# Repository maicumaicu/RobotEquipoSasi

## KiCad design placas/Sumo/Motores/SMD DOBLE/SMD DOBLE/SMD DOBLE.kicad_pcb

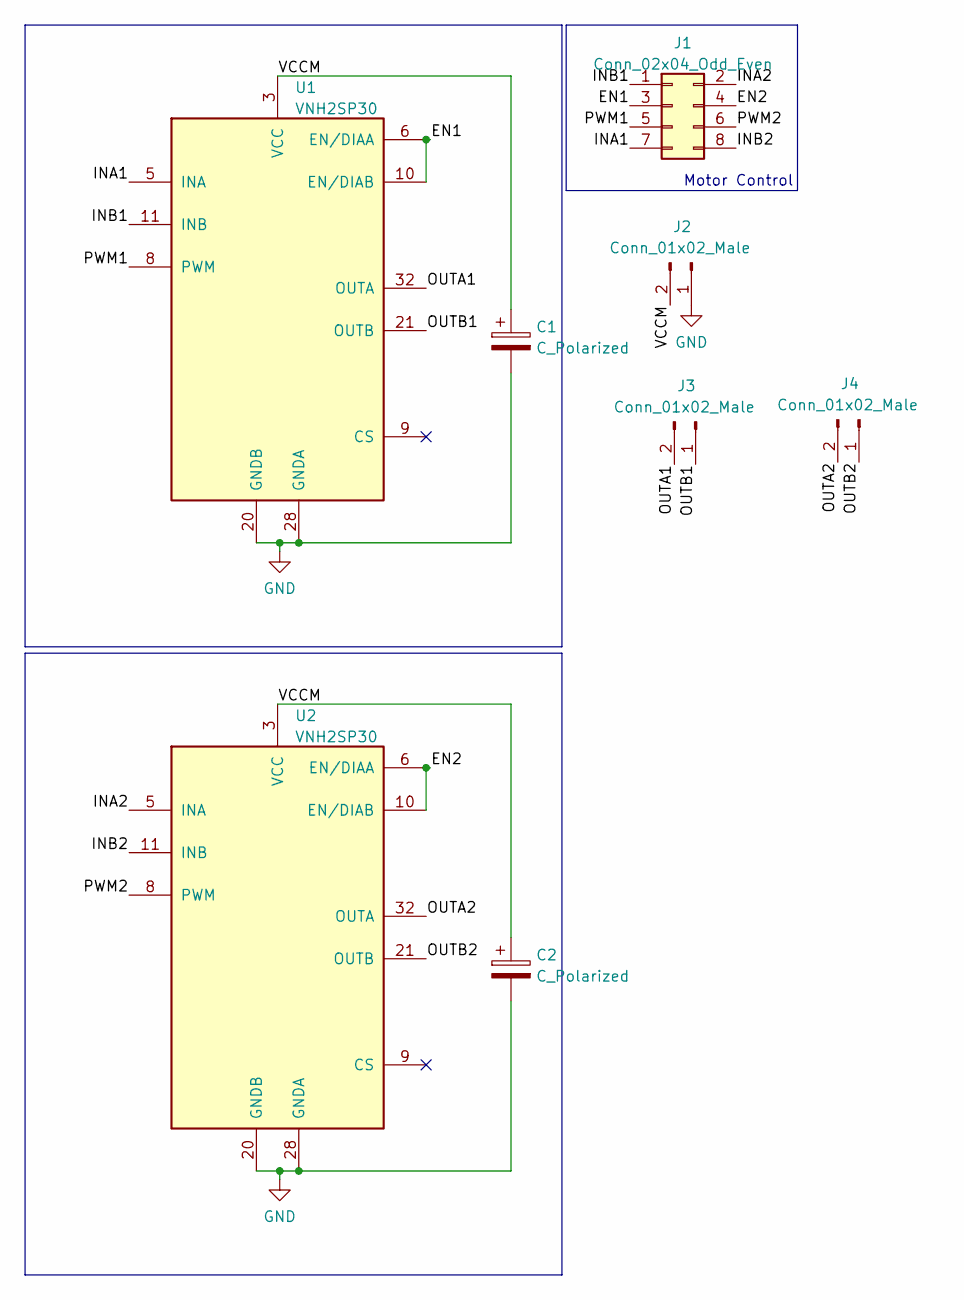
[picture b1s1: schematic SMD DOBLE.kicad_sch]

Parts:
C1, C2: C_Polarized; CP_Elec_5x5.3
J1: Conn_02x04_Odd_Even; IDC-Header_2x04_P2.54mm_Vertical
J2, J3, J4: Conn_01x02_Male; TerminalBlock_bornier-2_P5.08mm
U1, U2: VNH2SP30; ST_MultiPowerSO-30

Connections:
/EN1: J1.3, U1.6 (EN/DIAA), U1.10 (EN/DIAB)
/EN2: J1.4, U2.6 (EN/DIAA), U2.10 (EN/DIAB)
/INA1: J1.7, U1.5 (INA)
/INA2: J1.2, U2.5 (INA)
/INB1: J1.1, U1.11 (INB)
/INB2: J1.8, U2.11 (INB)
/OUTA1: J3.2, U1.1 (OUTA), U1.25 (OUTA), U1.30 (OUTA), U1.32 (OUTA)
/OUTA2: J4.2, U2.1 (OUTA), U2.25 (OUTA), U2.30 (OUTA), U2.32 (OUTA)
/OUTB1: J3.1, U1.15 (OUTB), U1.16 (OUTB), U1.21 (OUTB), U1.33 (OUTB)
/OUTB2: J4.1, U2.15 (OUTB), U2.16 (OUTB), U2.21 (OUTB), U2.33 (OUTB)
/PWM1: J1.5, U1.8 (PWM)
/PWM2: J1.6, U2.8 (PWM)
/VCCM: C1.1, C2.1, J2.2, U1.3 (VCC), U1.13 (VCC), U1.23 (VCC), U1.31 (VCC), U2.3 (VCC), U2.13 (VCC), U2.23 (VCC), U2.31 (VCC)
GND: C1.2, C2.2, J2.1, U1.18 (GNDB), U1.19 (GNDB), U1.20 (GNDB), U1.26 (GNDA), U1.27 (GNDA), U1.28 (GNDA), U2.18 (GNDB), U2.19 (GNDB), U2.20 (GNDB), U2.26 (GNDA), U2.27 (GNDA), U2.28 (GNDA)

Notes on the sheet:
Motor Control

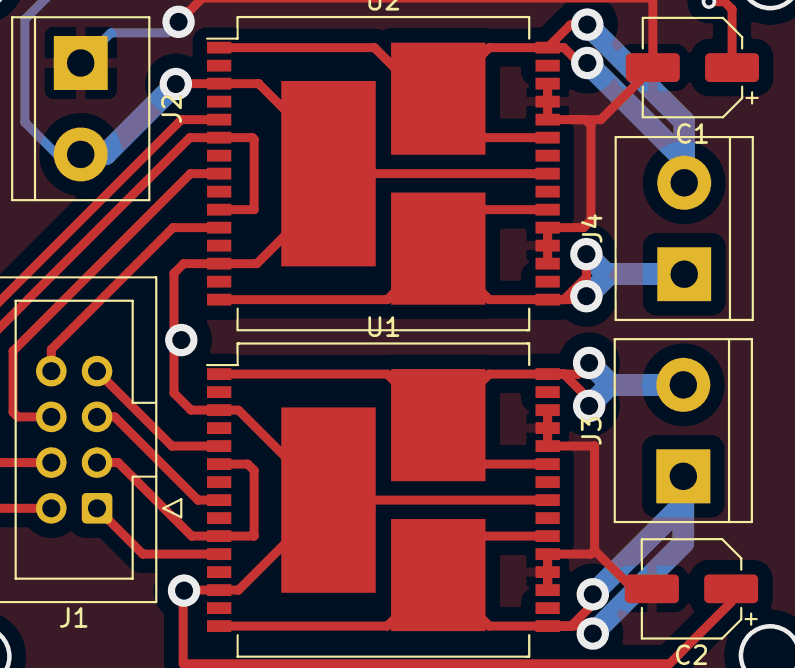
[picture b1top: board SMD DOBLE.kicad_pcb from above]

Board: 2 copper layers, 8 parts (0 on the bottom side), 14 nets.

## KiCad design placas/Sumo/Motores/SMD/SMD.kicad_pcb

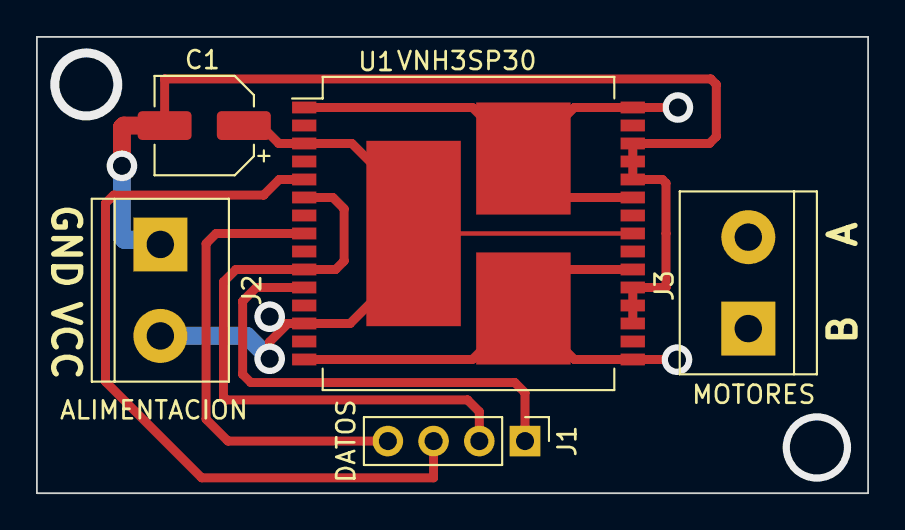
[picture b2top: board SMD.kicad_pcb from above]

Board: 2 copper layers, 46.2 x 25.3 mm, 5 parts (0 on the bottom side), 8 nets.

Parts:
C1: C_Polarized; CP_Elec_5x5.3
J1: DATOS; PinHeader_1x04_P2.54mm_Vertical
J2: ALIMENTACION; TerminalBlock_bornier-2_P5.08mm
J3: MOTORES; TerminalBlock_bornier-2_P5.08mm
U1: VNH3SP30; ST_MultiPowerSO-30

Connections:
/EN: J1.2, U1.6 (EN/DIAA), U1.10 (EN/DIAB)
/INA: J1.3, U1.5 (INA)
/INB: J1.1, U1.11 (INB)
/OUTA: J3.2, U1.1 (OUTA), U1.25 (OUTA), U1.30 (OUTA), U1.32 (OUTA)
/OUTB: J3.1, U1.15 (OUTB), U1.16 (OUTB), U1.21 (OUTB), U1.33 (OUTB)
/PWM: J1.4, U1.8 (PWM)
/VCCM: C1.1, J2.2, U1.3 (VCC), U1.13 (VCC), U1.23 (VCC), U1.31 (VCC)
GND: C1.2, J2.1, U1.18 (GNDB), U1.19 (GNDB), U1.20 (GNDB), U1.26 (GNDA), U1.27 (GNDA), U1.28 (GNDA)

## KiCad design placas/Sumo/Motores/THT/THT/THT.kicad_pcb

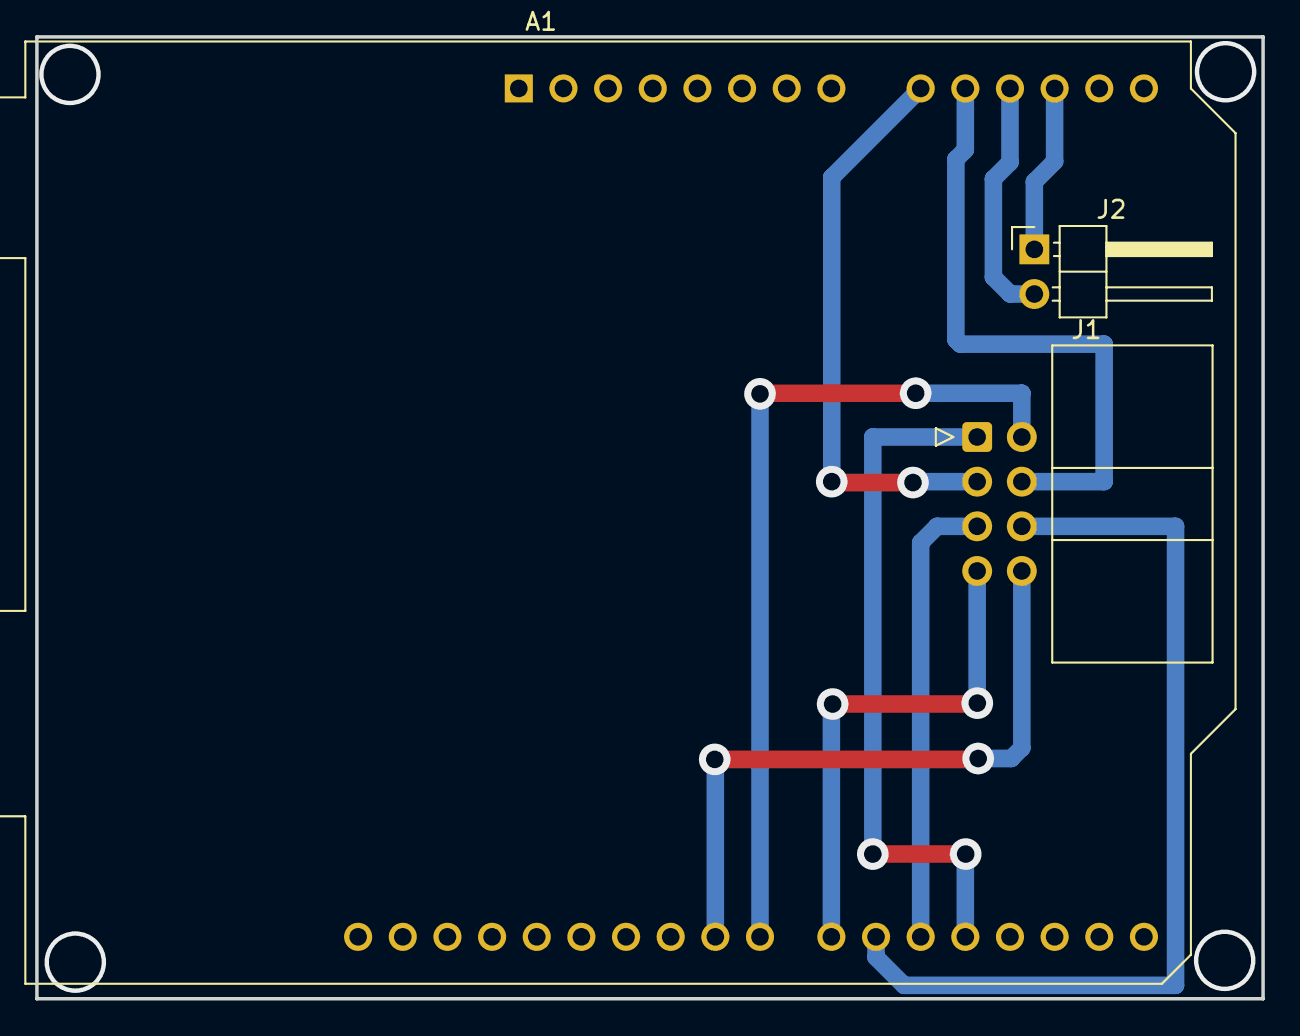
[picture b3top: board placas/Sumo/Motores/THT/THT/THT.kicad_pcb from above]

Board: 2 copper layers, 69.7 x 54.7 mm, 3 parts (0 on the bottom side), 10 nets.

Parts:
A1: Arduino_UNO_R3
J1: Control Motores; IDC-Header_2x04_P2.54mm_Horizontal
J2: Conn_01x02_Male; PinHeader_1x02_P2.54mm_Horizontal

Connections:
/C1: A1.11 (A2), J2.2
/C2: A1.12 (A3), J2.1
/EN1: A1.9 (A0), J1.3
/EN2: A1.10 (A1), J1.4
/INA1: A1.22 (D7), J1.7
/INA2: A1.23 (D8), J1.2
/INB1: A1.19 (D4), J1.1
/INB2: A1.24 (D9), J1.8
/PWM1: A1.20 (D5), J1.5
/PWM2: A1.21 (D6), J1.6

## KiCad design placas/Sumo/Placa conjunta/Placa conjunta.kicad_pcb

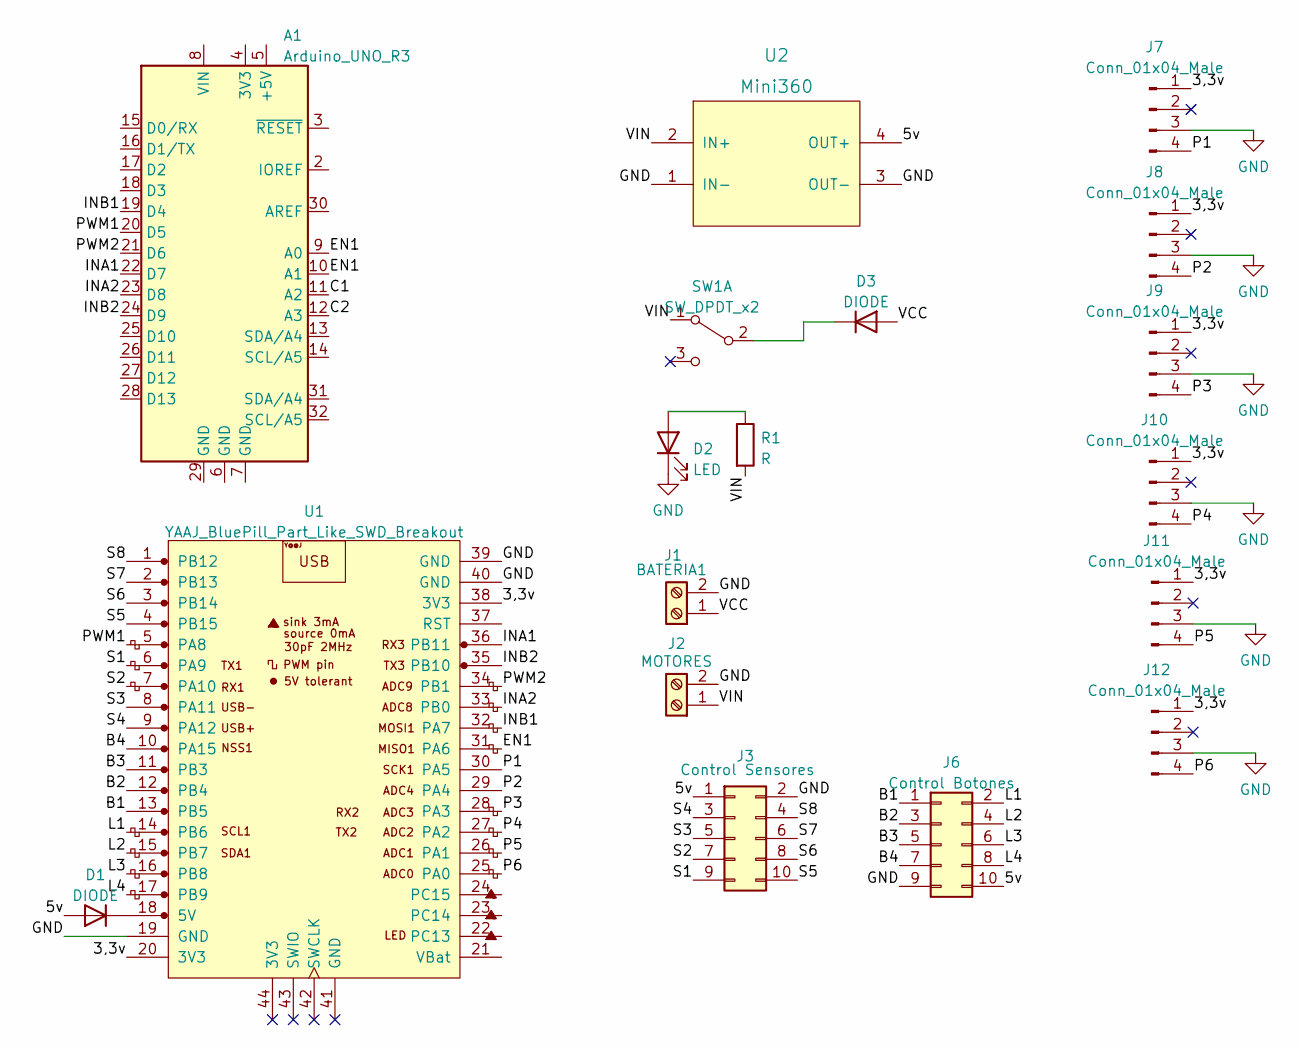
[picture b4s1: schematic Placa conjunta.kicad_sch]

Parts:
A1: Arduino_UNO_R3
D1, D3: DIODE; D_5W_P12.70mm_Horizontal
D2: LED; LED_D3.0mm
J1: BATERIA1; DEANS
J2: MOTORES; DEANS
J3: Control Sensores; IDC-Header_2x05_P2.54mm_Vertical
J6: Control Botones; IDC-Header_2x05_P2.54mm_Vertical
J7, J8, J9, J10, J11, J12: Conn_01x04_Male; JST_XH_B4B-XH-A_1x04_P2.50mm_Vertical
R1: R; R_Axial_DIN0207_L6.3mm_D2.5mm_P10.16mm_Horizontal
SW1: SW_DPDT_x2; Banana_Jack_3Pin
U1: YAAJ_BluePill_Part_Like_SWD_Breakout; YAAJ_BluePill_1
U2: Mini360; Mini360_step-down

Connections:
/3,3v: J7.1, J8.1, J9.1, J10.1, J11.1, J12.1, U1.20 (3V3), U1.38 (3V3)
/5v: D1.1 (A), J3.1, J6.10, U2.4 (OUT+)
/B1: J6.1, U1.13 (PB5)
/B2: J6.3, U1.12 (PB4)
/B3: J6.5, U1.11 (PB3)
/B4: J6.7, U1.10 (PA15)
/C1: A1.11 (A2)
/C2: A1.12 (A3)
/EN1: A1.9 (A0), A1.10 (A1), U1.31 (PA6)
/INA1: A1.22 (D7), U1.36 (PB11)
/INA2: A1.23 (D8), U1.33 (PB0)
/INB1: A1.19 (D4), U1.32 (PA7)
/INB2: A1.24 (D9), U1.35 (PB10)
/L1: J6.2, U1.14 (PB6)
/L2: J6.4, U1.15 (PB7)
/L3: J6.6, U1.16 (PB8)
/L4: J6.8, U1.17 (PB9)
/P1: J7.4, U1.30 (PA5)
/P2: J8.4, U1.29 (PA4)
/P3: J9.4, U1.28 (PA3)
/P4: J10.4, U1.27 (PA2)
/P5: J11.4, U1.26 (PA1)
/P6: J12.4, U1.25 (PA0)
/PWM1: A1.20 (D5), U1.5 (PA8)
/PWM2: A1.21 (D6), U1.34 (PB1)
/S1: J3.9, U1.6 (PA9)
/S2: J3.7, U1.7 (PA10)
/S3: J3.5, U1.8 (PA11)
/S4: J3.3, U1.9 (PA12)
/S5: J3.10, U1.4 (PB15)
/S6: J3.8, U1.3 (PB14)
/S7: J3.6, U1.2 (PB13)
/S8: J3.4, U1.1 (PB12)
/VCC: D3.1 (A), J1.1
/VIN: J2.1, R1.2, SW1.1 (A), U2.2 (IN+)
GND: D2.1 (K), J1.2, J2.2, J3.2, J6.9, J7.3, J8.3, J9.3, J10.3, J11.3, J12.3, U1.19 (GND), U1.39 (GND), U1.40 (GND), U2.1 (IN-), U2.3 (OUT-)
unnamed: D1.2 (K), U1.18 (5V)
unnamed: D2.2 (A), R1.1
unnamed: D3.2 (K), SW1.2 (B)

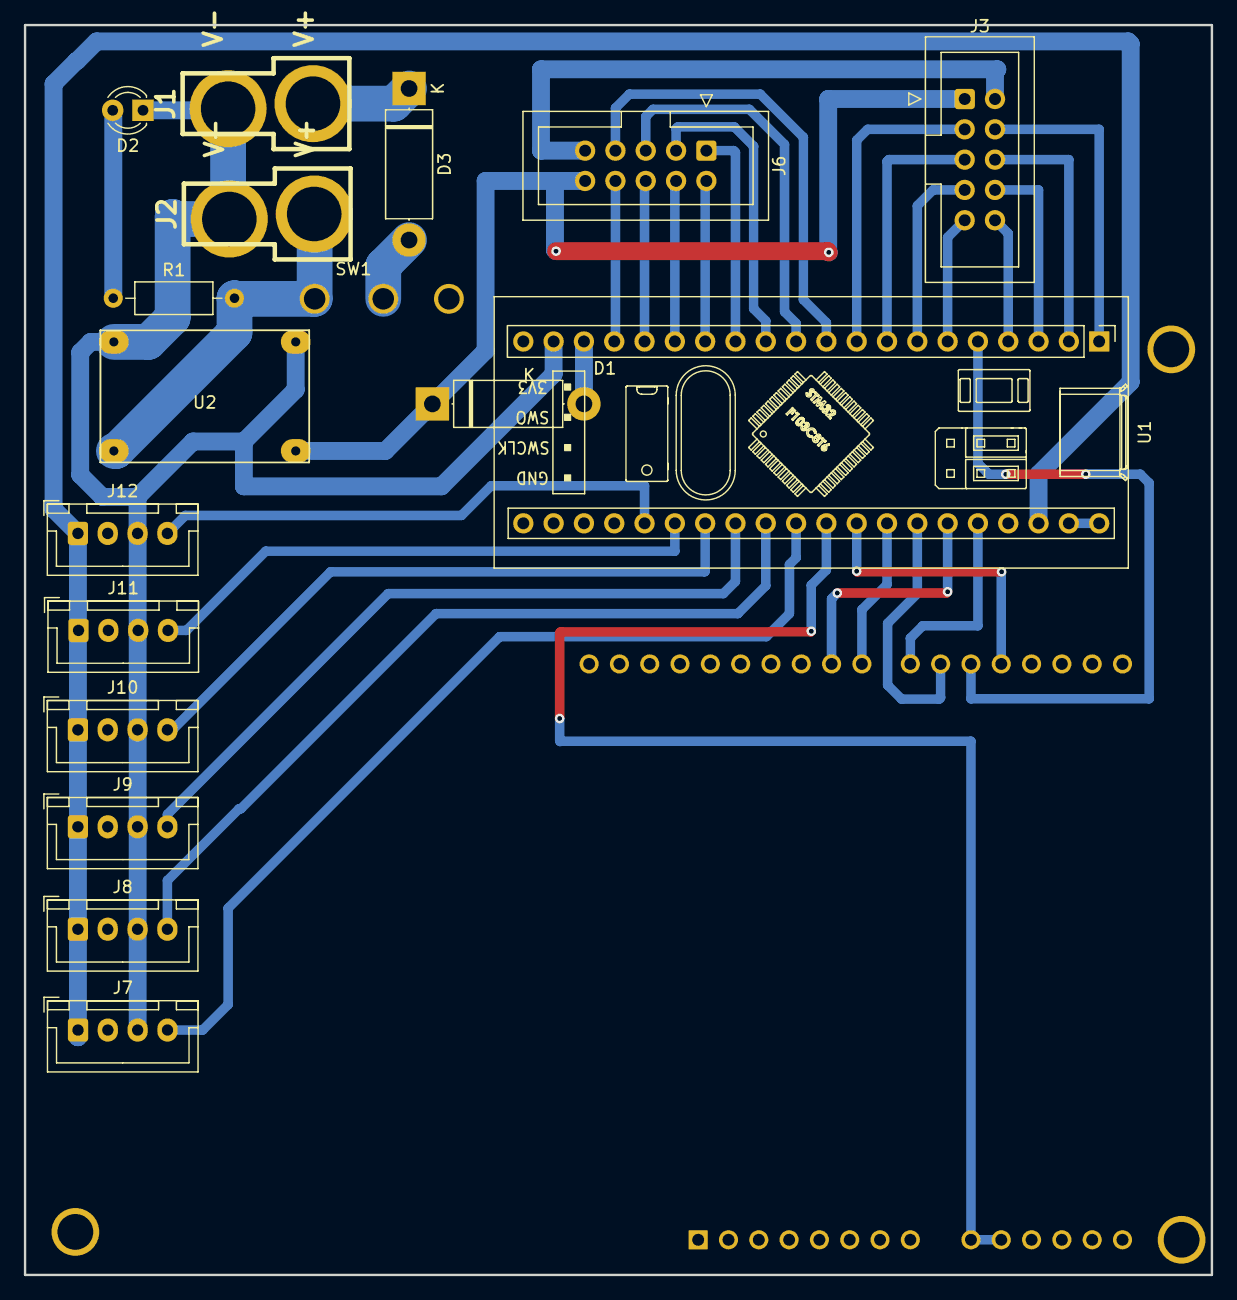
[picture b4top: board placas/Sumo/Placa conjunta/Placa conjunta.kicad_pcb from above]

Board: 2 copper layers, 99.5 x 104.7 mm, 18 parts (1 on the bottom side), 37 nets.

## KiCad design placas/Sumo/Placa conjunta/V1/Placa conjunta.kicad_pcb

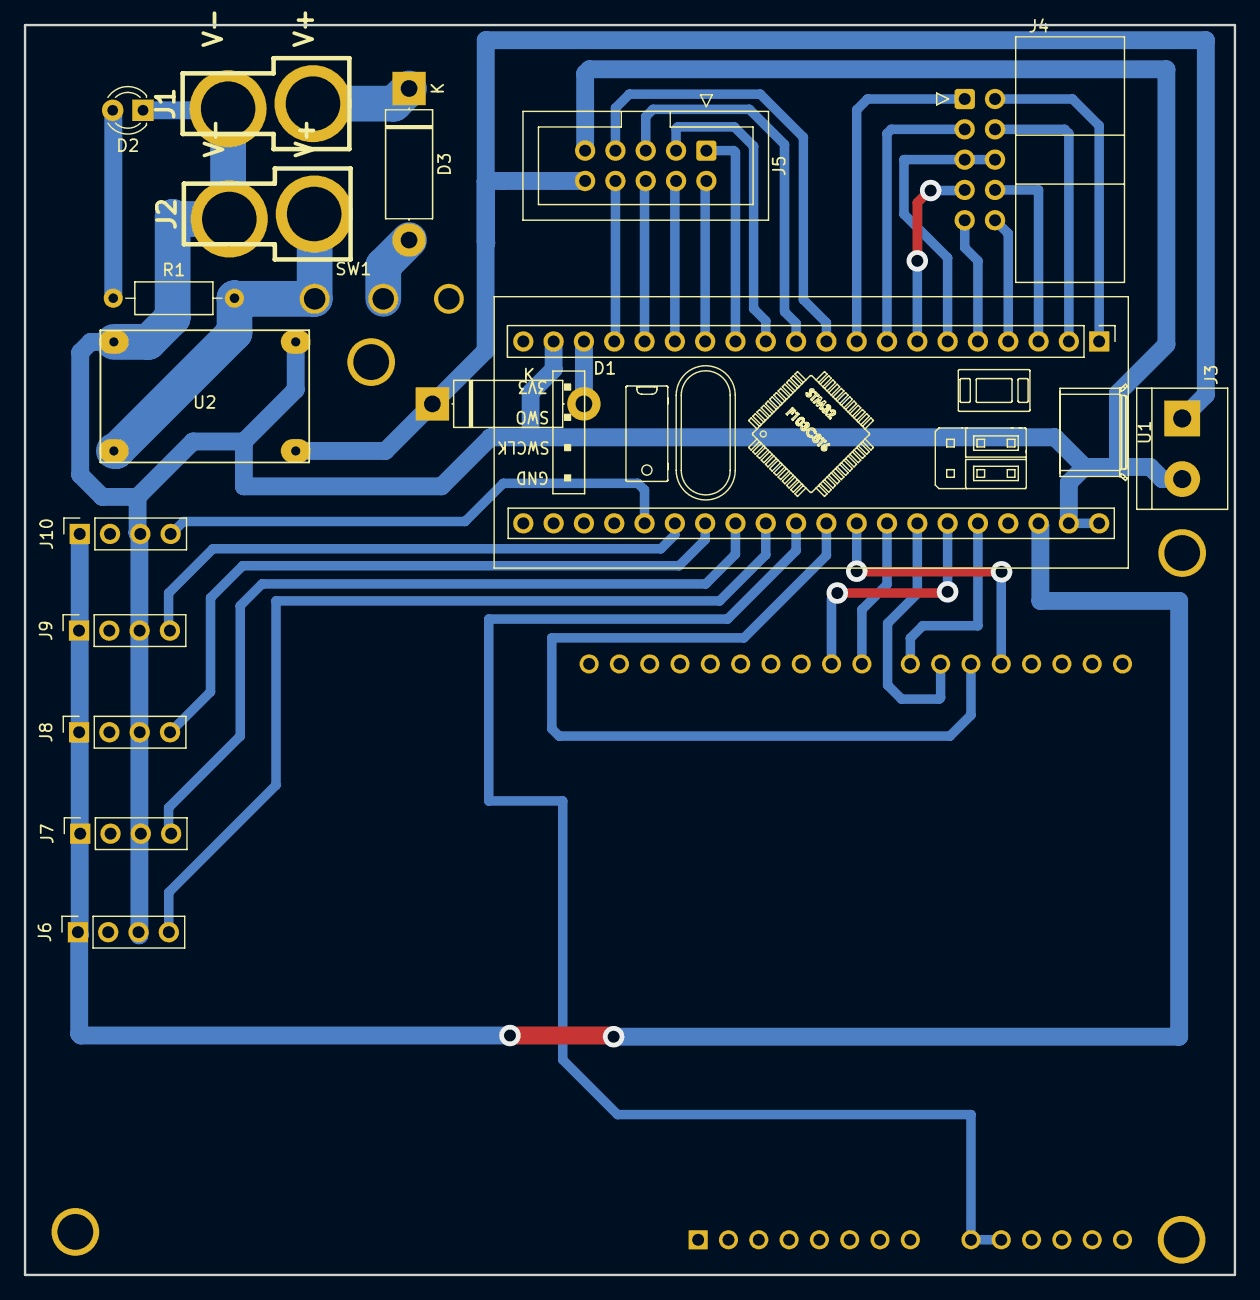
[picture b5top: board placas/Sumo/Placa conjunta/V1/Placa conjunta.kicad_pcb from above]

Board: 2 copper layers, 101.4 x 104.7 mm, 18 parts (1 on the bottom side), 37 nets.

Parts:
A1: Arduino_UNO_R3
D1, D3: DIODE; D_5W_P12.70mm_Horizontal
D2: LED; LED_D3.0mm
J1: BATERIA1; DEANS
J2: MOTORES; DEANS
J3: Conn_01x02_Male; TerminalBlock_bornier-2_P5.08mm
J4: Control Sensores; IDC-Header_2x05_P2.54mm_Horizontal
J5: Control Botones; IDC-Header_2x05_P2.54mm_Vertical
J6, J7, J8, J9, J10: Conn_01x04_Male; PinSocket_1x04_P2.54mm_Vertical
R1: R; R_Axial_DIN0207_L6.3mm_D2.5mm_P10.16mm_Horizontal
SW1: SW_DPDT_x2; Banana_Jack_3Pin
U1: YAAJ_BluePill_Part_Like_SWD_Breakout; YAAJ_BluePill_1
U2: Mini360; Mini360_step-down

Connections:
/3,3v: J6.1, J7.1, J8.1, J9.1, J10.1, U1.20 (3V3), U1.38 (3V3)
/5v: D1.1 (A), J3.1, J5.10, U2.4 (OUT+)
/38khz: J4.5, J4.6, U1.6 (PA9)
/B1: J5.1, U1.13 (PB5)
/B2: J5.3, U1.12 (PB4)
/B3: J5.5, U1.11 (PB3)
/B4: J5.7, U1.10 (PA15)
/EN1: A1.9 (A0), A1.10 (A1), U1.30 (PA5)
/INA1: A1.22 (D7), U1.36 (PB11)
/INA2: A1.23 (D8), U1.33 (PB0)
/INB1: A1.19 (D4), U1.32 (PA7)
/INB2: A1.24 (D9), U1.35 (PB10)
/L1: J5.2, U1.14 (PB6)
/L2: J5.4, U1.15 (PB7)
/L3: J5.6, U1.16 (PB8)
/L4: J5.8, U1.17 (PB9)
/P1: J6.4, U1.29 (PA4)
/P2: J7.4, U1.28 (PA3)
/P3: J8.4, U1.27 (PA2)
/P4: J9.4, U1.26 (PA1)
/P5: J10.4, U1.25 (PA0)
/PWM1: A1.20 (D5), U1.31 (PA6)
/PWM2: A1.21 (D6), U1.34 (PB1)
/S1: J4.9, U1.5 (PA8)
/S2: J4.7, U1.7 (PA10)
/S3: J4.3, U1.8 (PA11)
/S4: J4.1, U1.9 (PA12)
/S5: J4.10, U1.4 (PB15)
/S6: J4.8, U1.3 (PB14)
/S7: J4.4, U1.2 (PB13)
/S8: J4.2, U1.1 (PB12)
/VCC: D3.1 (A), J1.1
/VIN: J2.1, R1.2, SW1.1 (A), U2.2 (IN+)
GND: D2.1 (K), J1.2, J2.2, J3.2, J5.9, J6.3, J7.3, J8.3, J9.3, J10.3, U1.19 (GND), U1.39 (GND), U1.40 (GND), U2.1 (IN-), U2.3 (OUT-)
unnamed: D1.2 (K), U1.18 (5V)
unnamed: D2.2 (A), R1.1
unnamed: D3.2 (K), SW1.2 (B)

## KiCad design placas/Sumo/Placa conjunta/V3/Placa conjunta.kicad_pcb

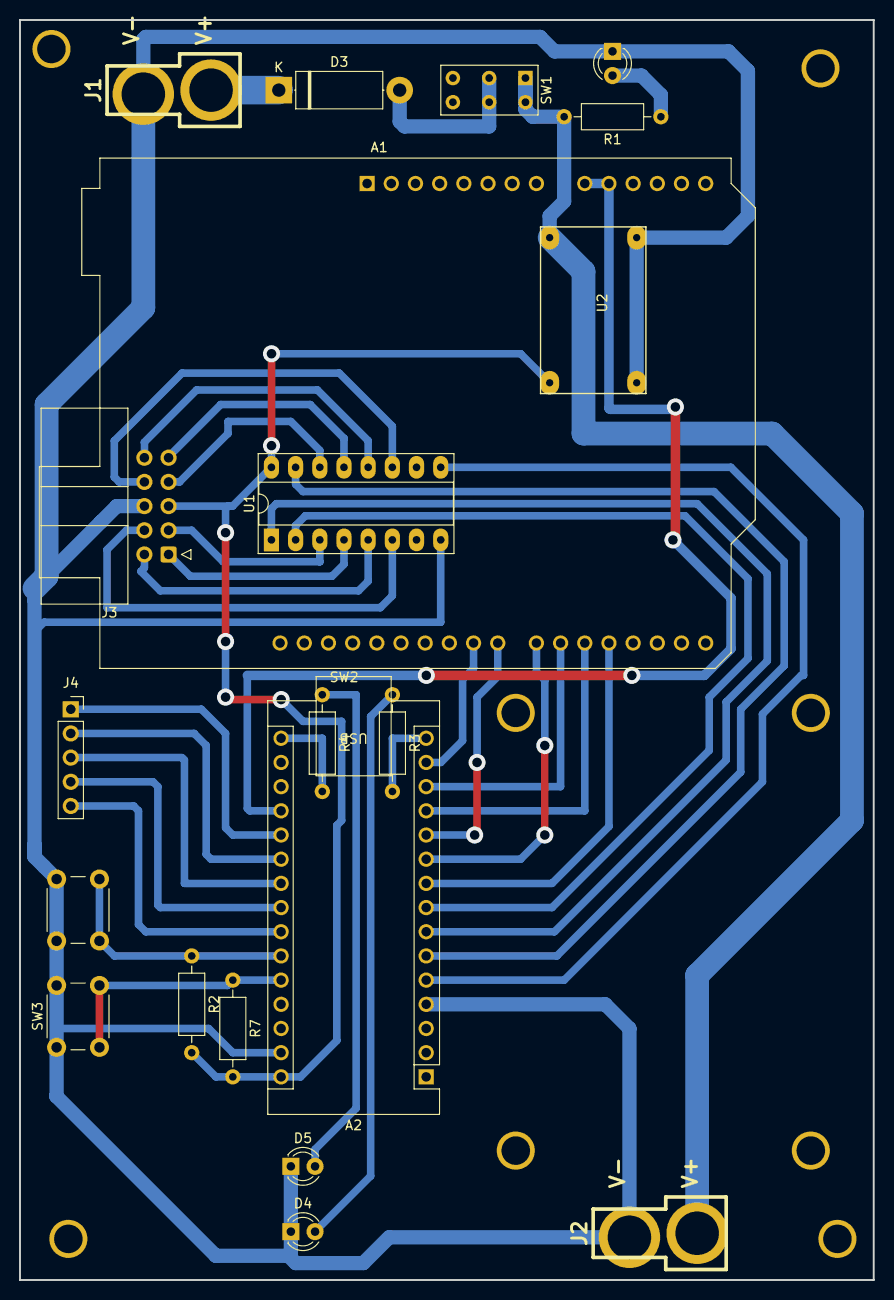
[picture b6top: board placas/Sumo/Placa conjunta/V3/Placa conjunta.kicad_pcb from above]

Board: 2 copper layers, 89.7 x 132.3 mm, 20 parts (0 on the bottom side), 36 nets.

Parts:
A1: Arduino_UNO_R3
A2: Arduino_Nano_v3.x; Arduino_Nano
D2, D4, D5: LED; LED_D3.0mm
D3: type="D" model="DIODE" lib=""; D_5W_P12.70mm_Horizontal
J1: BATERIA1; DEANS
J2: MOTORES; DEANS
J3: Control Sensores; IDC-Header_2x05_P2.54mm_Horizontal
J4: Conn_01x05_Pin; PinSocket_1x05_P2.54mm_Vertical
R1, R2, R7: R; R_Axial_DIN0207_L6.3mm_D2.5mm_P10.16mm_Horizontal
R3, R4: 1000; R_Axial_DIN0207_L6.3mm_D2.5mm_P10.16mm_Horizontal
SW1: SW_DPDT_x2; SW_NKK_G1xJP
SW2, SW3: SW_Push; SW_PUSH_6mm
U1: 74LS165; DIP-16_W7.62mm_Socket_LongPads
U2: Mini360; Mini360_step-down

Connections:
/5v: A2.30 (VIN), J3.5, R2.2, R7.2, U1.16 (VCC), U2.4 (OUT+)
/B1: A2.25 (A6), R2.1, SW2.2
/B2: A2.26 (A7), R7.1, SW3.2
/CEP(D15): A2.6 (D3), U1.15 (~CE)
/CP(D4): A2.8 (D5), U1.2 (CP)
/EN1: A1.9 (A0), A1.10 (A1), A2.19 (A0)
/INA1: A1.22 (D7), A2.10 (D7)
/INA2: A1.23 (D8), A2.11 (D8)
/INB1: A1.19 (D4), A2.9 (D6)
/INB2: A1.24 (D9), A2.14 (D11)
/L1: A2.15 (D12), R3.2
/L2: A2.16 (D13), R4.2
/LP(D5): A2.7 (D4), U1.1 (~PL)
/P1: A2.20 (A1), J4.1
/P2: A2.21 (A2), J4.2
/P3: A2.22 (A3), J4.3
/P4: A2.23 (A4), J4.4
/P5: A2.24 (A5), J4.5
/PWM1: A1.20 (D5), A2.12 (D9)
/PWM2: A1.21 (D6), A2.13 (D10)
/S1: J3.9, U1.13 (D2)
/S2: J3.7, U1.14 (D3)
/S3: J3.3, U1.3 (D4)
/S4: J3.1, U1.4 (D5)
/S5: J3.10, U1.12 (D1)
/S6: J3.8, U1.11 (D0)
/S7: J3.4, U1.6 (D7)
/S8: J3.2, U1.5 (D6)
/Salida: A2.5 (D2), U1.9 (Q7)
/VCC: D3.1 (A), J1.1
/VIN: J2.1, R1.2, SW1.1 (A), U2.2 (IN+)
GND: A2.4 (GND), A2.29 (GND), D2.1 (K), D4.1 (K), D5.1 (K), J1.2, J2.2, J3.6, SW2.1, SW3.1, U1.8 (GND), U2.1 (IN-), U2.3 (OUT-)
unnamed: D2.2 (A), R1.1
unnamed: D3.2 (K), SW1.2 (B)
unnamed: D4.2 (A), R3.1
unnamed: D5.2 (A), R4.1

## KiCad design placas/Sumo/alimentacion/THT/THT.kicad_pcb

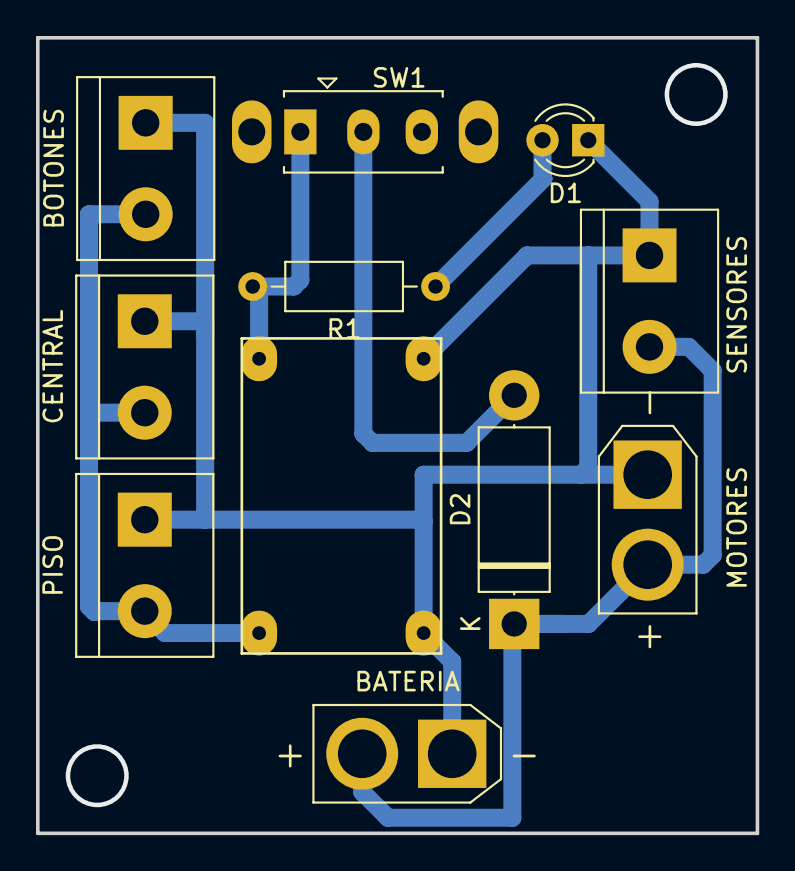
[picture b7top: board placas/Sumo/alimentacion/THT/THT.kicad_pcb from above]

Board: 2 copper layers, 40.0 x 44.2 mm, 11 parts (0 on the bottom side), 6 nets.

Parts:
D1: LED; LED_D3.0mm
D2: DIODE; D_5W_P12.70mm_Horizontal
J1: SENSORES; TerminalBlock_bornier-2_P5.08mm
J2: MOTORES; AMASS_XT30U-F_1x02_P5.0mm_Vertical
J3: BOTONES; TerminalBlock_bornier-2_P5.08mm
J4: CENTRAL; TerminalBlock_bornier-2_P5.08mm
J5: PISO; TerminalBlock_bornier-2_P5.08mm
J6: BATERIA; AMASS_XT30U-F_1x02_P5.0mm_Vertical
R1: R; R_Axial_DIN0207_L6.3mm_D2.5mm_P10.16mm_Horizontal
SW1: SW_DPDT_x2; SW_Slide_1P2T_CK_OS102011MS2Q
U1: Mini360; Mini360_step-down

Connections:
/5v: J3.2, J4.2, J5.2, U1.4 (OUT+)
/VCC: D2.1 (A), J1.2, J2.2, J6.2
/VIN: R1.2, SW1.1 (A), U1.2 (IN+)
GND: D1.1 (K), J1.1, J2.1, J3.1, J4.1, J5.1, J6.1, U1.1 (IN-), U1.3 (OUT-)
unnamed: D1.2 (A), R1.1
unnamed: D2.2 (K), SW1.2 (B)
